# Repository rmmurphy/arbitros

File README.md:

# Introduction
_Arbitros_ (pronounced are-bee-trose) is a lightweight real time operating system developed initially—but not solely— for the Atmel XMEGA 8/16-bit series microcontroller. The name _arbitros_ is a fusion between the Latin arbitror (meaning to judge or decide) and OS (operating system). The software was developed over three years of meticulous work and is comprised of five thoroughly tested modular core components named **RTOS**, **HAL**, **UTILITIES**, **DRIVERS**, and **PACKAGES**. These components were designed to abstract common functionality, providing a user-space application with a modular, readable, layered architecture as seen in the figure below.

## Modular Core Components

### RTOS

The RTOS module performs kernel operations such as thread, semaphore, and file management;in addition to priority based task switching, driver management, time management, error handling, inter-thread communication (mailboxing), watchdog management, system debug management, and system terminal control.

### HAL

The hardware abstraction layer provides a common interface for an application when communicating with the following device specific peripherals: ADCs, clocks, DMAs, EEPROM, GPIOs, PMIC, SPIs, timers, TWIs, UARTs, and watchdog timers.

### UTILITIES

The UTILITIES module consists of software designed to help with common programming tasks such as buffer, linked-list, and state-machine management. Additionally, the module contains a mathematical library designed to perform floating and fixed-point operations such as multiply, divide, cos, sin, atan2, log10, alog10, and sqrt. In addition to these common math routines, the package contains software for performing floating point matrix operations such as inversion, transposition, addition, subtraction, multiplication, division, normalization, and eigenvalue decomposition.

### DRIVERS

A collection of Linux inspired device drivers that control a variety of external components such as Sparkfun’s 9 DOF sensor module, Newhaven’s serial character LCD module, a generic pan/tilt servo, micro SD cards, sonar modules, the RN-XV wifly module, and a terminal window controller.

### PACKAGES

External open source libraries such as libfat32, modified to operate within the _arbitros_ framework.

## Designed with Portability in Mind

Although _arbitros_ currently works with the Atmel atxmega128A1, the software was designed to be completely portable—simply modify the contents of the ‘HAL’ layer in order to port the core components to a multitude of processor architectures.

# Why was _arbitros_ Created?

## Easy to use and rich in capability

_Abitros_ was created to fit a gap in the hobbyist market. Development platforms such as Arduino were originally designed for individuals with minimal or no programming experience. As a result, their monolithic software architecture is limiting—lacking many of the features of a higher level multi-threaded operating environment. Conversely, single board computers like Raspberry Pi’s were intended for experienced programmers providing a richer set of capability; however, setting up the build environment (installing the root file system and cross compilation tools) to run Linux is a daunting task—even for seasoned professionals. 
_Arbitros_ combines the best attributes of Arduino—simplicity—with that of Linux based systems—capability—in one easy to use package. 

## Standardized Software Interfaces
Unlike Arduino, _arbitros_ incorporates Linux inspired function calls such as open, close, read, write, and ioctl in order to abstract–from the user–the intricate details that define how a driver communicates with an off-chip device (such as a shield). As seen in the example below, this framework allows a user-space application to interact with a particular entity–for instance a WIFI module–without having to know the specific details about how the device is controlled (such as the particular UART and GPIO ports used). Furthermore, this driver "blue print" makes it easier for a hobbyist to upgrade external hardware capability without effecting existing _arbitros_ user-space software applications. For example, imagine that a hobbyist has developed an _arbitros_ application that controls an autonomous vehicle using inputs from Sparkfun’s 9DOF sensor module . At a future date the hobbyist decides to upgrade the IMU to a newer more capable model. With _arbitros_ this is easy, the hobbyist simply swaps the old device driver for the new one–without requiring changes to his/her user-space application software. 

# What Runs _arbitros_?
## Sparkfun XMega100 Breakout, Atmel XMEGA-A1 Xplained, and Primus Development Board

In order to highlight the capability of _arbitros_ a development board named _Primus_ was created. As seen in the picture, _Primus_ evolved from Sparkfun’s XMega100 Breakout board (https://www.sparkfun.com/products/9546) and the architecture was designed using Sparkfun’s design rules and Eagle parts library. Although _Primus_ is a more robust solution (offering PDI debugging, USB console, and a fat32 filesystem) _arbitros_ can still operate on Sparkfun's XMega100 Breakout and Atmel's XMEGA-A1 Xplained (http://www.atmel.com/tools/XMEGA-A1XPLAINED.aspx).

# What can _arbitros_ do?
## Console with Fat32 File System

As seen in the putty window, _abitros_ offers a rich set of Linux inspired console commands. The first directive ’ls’, outputs a list of all directories and files currently stored on the SD card. In this example, only the 'LOGS' directory with the file 'DMSG.TXT' is present. These particular files are created during system initialization and used by the kernel for logging debug ‘printf’ messages. Looking closely at the terminal output, one can see that directories are traversed in a familiar way via the ‘cd’ command. In order to promote readability, the root directory is highlighted green and all subsequent directories are highlighted red. The third directive ’help’ tells the system to display a list of the sytem commands recognized by the kernel. Finally, the instruction ’dev’, displays a list of device drivers registered with the kernel and their corresponding number of open handles. In this example only the  status (LED controller), console, and SD drivers have been registered.

Looking closely at the second figure below, the command ’top’ displays metrics describing the size of various memory sections (.data, .bss, and .heap) including the amount RAM left on the system. Additionally, ’top’ shows an estimate of processor loading, which is comprised of metrics averaged over a one and five minute interval. This feature allows an _abitros_ developer to tune the performance of a particular thread or collection of threads in order to minimize the burden on the system. The instruction ’sdl’ with argument 0,1, or 2 turns on one of the kernel’s three prioritized debug levels. As seen in the example, ’sdl 0’ enables the lowest priority debug level, displaying a message every time the ‘idle’ thread resets the system watchdog timer. Increasing the debug level, such as configuring ’sdl 1’ (or 2), will tell the kernel to print all messages with the same or higher priority. The ability to display debug messages based on priority eases software integration, allowing a developer to "de-clutter" the terminal output by informing the kernel to highlight the most important information. The final command ’head’, tells the kernel to print the contents of one of the files stored on the SD card. As seen in the example, the debug log was displayed ( ‘/logs/dmsg.txt’), showing the results from the previous ‘sdl 0’ debug session.

## Attitude Heading Reference System Sensor Fusion

As part of the core ‘DRIVERS’ package, _abitros_ offers a device driver designed to fuse the measurements from Sparkfun’s 9DOF sensor module using a 9-state fixed-point error-state Kalman filter. Unlike other hobbyist sensor fusion systems available on the market , _abitros‘_ Kalman filter was designed using fixed-point rather than floating point notation. This methodology decreases processor loading enabling the algorithm to update at rates in excess of 50msec—vastly improving  the tracking capability of fast maneuvering objects. Moreover, the Kalman filter not only corrects for attitude and heading error, but it corrects gyro  bias and axis misalignment as well. In addition to the nominal filtering operations, the device driver performs magnetometer and accelerometer calibration using a ellipsoid fitting routine. Again, unlike other open source AHRS systems that perform calibration external to the microcontroller (using Matlab); _abitros‘_ AHRS performs the calibration natively using matrix operations from its built in math library (utl_math.c) provided in the ‘UTILITIES’ package. 

## Interactive AHRS GUI (arhsGui.py)

In order to demonstrate the capability of _abitros’_ sensor fusion system, an interactive graphical user interface was created using a combination of Pyqt and Pyopengl. As seen in the figure, the GUI displays three main views. The first view (‘3D’), shows a 3D orientation of the sensor along with heading (i.e. compass) and roll/pitch instrumentation. The second view (‘XY’), displays real-time plots of the roll, pitch, and yaw. Colors are used to differentiate measurement types  with green representing raw meter readings, yellow representing Kalman filtered readings, and red highlighting the difference between filtered and non-filtered measurements. The final view ‘Calibration’, controls calibration of the magnetometer and accelerometer showing the pre and post calibration data by way of the green and red point cloud.

# Getting started

The examples directory (https://github.com/rmmurphy/arbitros/raw/master/boards/primus/examples) has three folders containing software–with accompanying Atmel Studio 6 projects (http://www.atmel.com/microsite/atmel_studio6) —that demonstrate the capability of the _abitros_ operating system and _Primus_ development board. The first folder, ‘ins’, contains the AHRS software and Python GUI discussed in detail in the section titled, **What can _arbitros_ do?**. The second folder, ‘mathEval’, provides software comparing the performance differences between _abitros’_ native math library (utl_math.c) and the standard ANSII mathematics library (math.h). The final folder, ‘primusEval’, provides examples on using various _abitros_ software components such as semaphores, mailbox modules, and peripherals.

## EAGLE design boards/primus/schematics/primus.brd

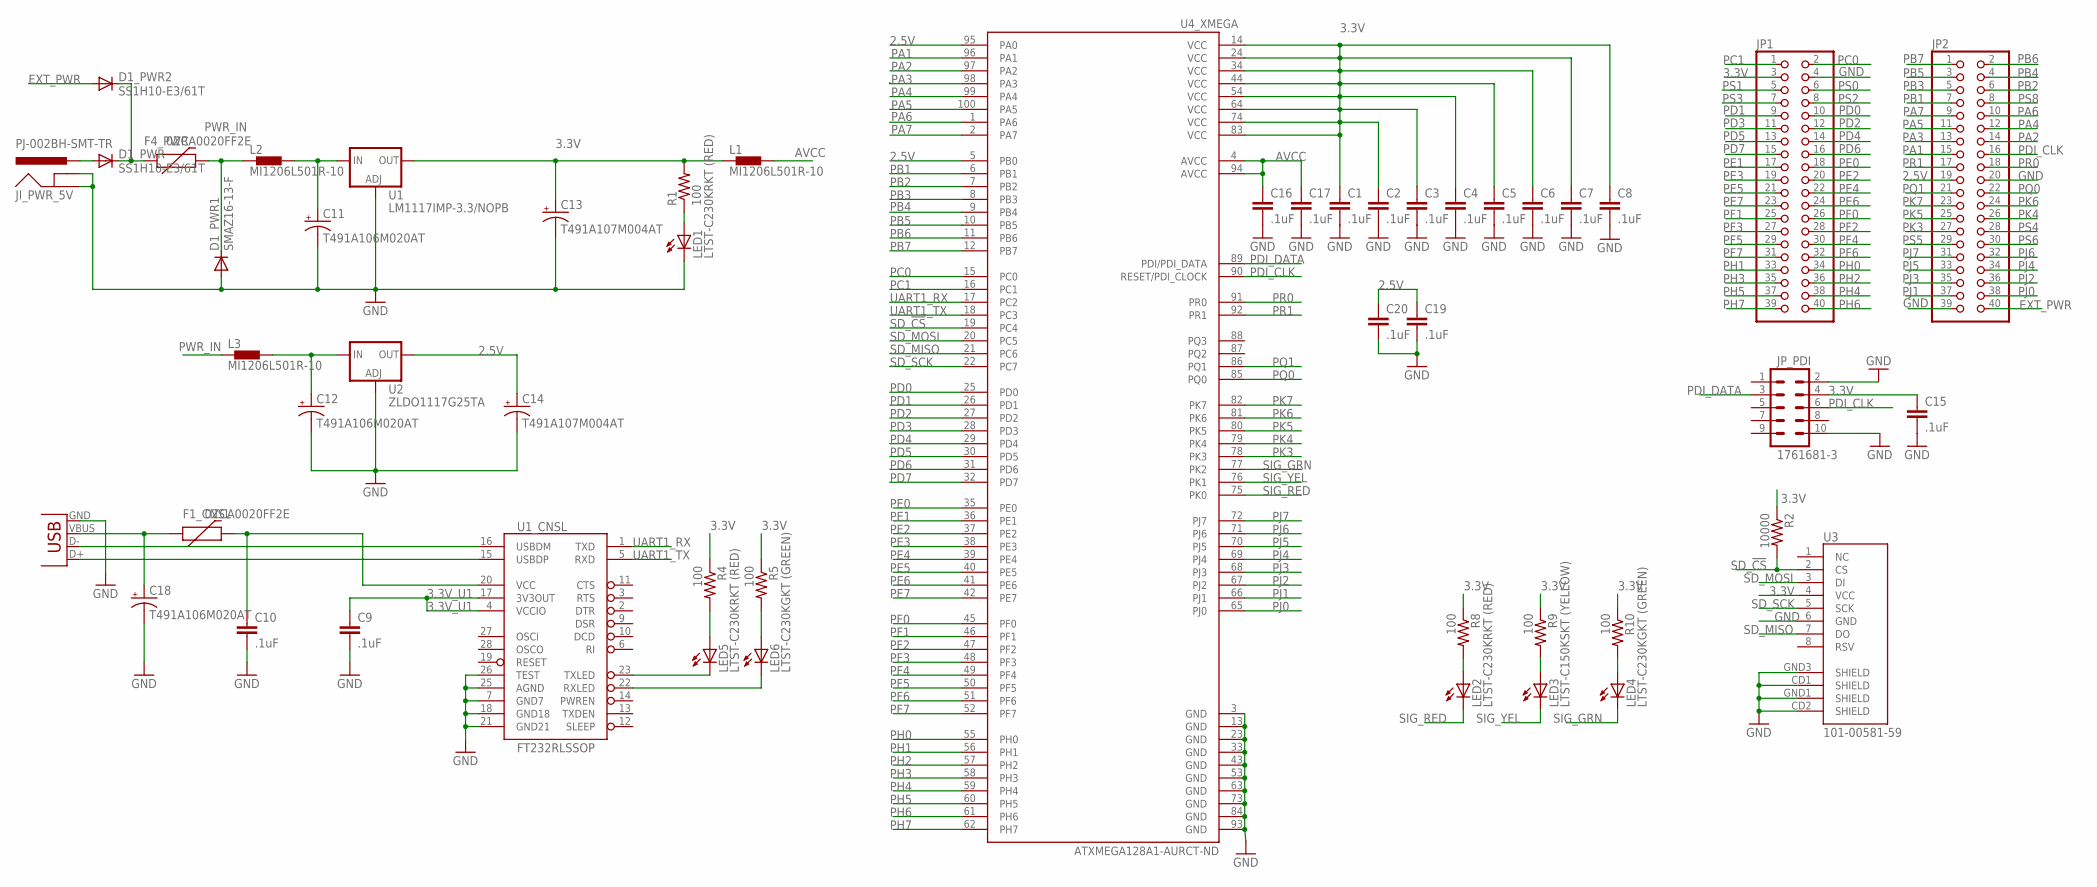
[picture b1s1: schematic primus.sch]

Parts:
C1, C2, C3, C4, C5, C6, C7, C8, C9, C10, C15, C16, C17, C19, C20: .1uF; 0603-CAP
C11, C12, C18: T491A106M020AT; EIA3216
C13, C14: T491A107M004AT; EIA3216
D1_PWR, D1_PWR2: SS1H10-E3/61T; SMA-DIODE
D1_PWR1: SMAZ16-13-F; SMA-DIODE
F1_CNSL, F4_PWR: 0ZCA0020FF2E; PTC-1206
JI_PWR_5V: PJ-002BH-SMT-TR; POWER_JACK_SMD
JP1, JP2: PINHD-2X20; 2X20
JP_PDI: 1761681-3; 2X5-SHROUDED
L1, L2, L3: MI1206L501R-10; 1206
LED1, LED2, LED5: LTST-C230KRKT (RED); LED-1206
LED3: LTST-C150KSKT (YELLOW); LED-1206
LED4, LED6: LTST-C230KGKT (GREEN); LED-1206
R1, R4, R5, R8, R9, R10: 100; 0603-RES
R2: 10000; 0603-RES
U1: LM1117IMP-3.3/NOPB; SOT223
U1_CNSL: FT232RLSSOP; SSOP28DB
U2: ZLDO1117G25TA; SOT223
U3: 101-00581-59; MICRO-SD-SOCKET-PP
U4_XMEGA: ATXMEGA128A1-AURCT-ND; TQFP-100-14X14MM
X2_CNSL: UX60A-MB-5ST; USB-MINIB

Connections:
2.5V: C14.A (+), C19.1, C20.1, JP2.19, U2.2 (OUT), U4_XMEGA.5 (PB0), U4_XMEGA.95 (PA0)
3.3V: C1.1, C2.1, C3.1, C4.1, C5.1, C6.1, C7.1, C8.1, C13.A (+), C15.1, JP1.3, JP_PDI.4, L1.1, R1.2, R2.1, R4.1, R5.1, R8.1, R9.1, R10.1, U1.2 (OUT), U3.4 (VCC), U4_XMEGA.14 (VCC), U4_XMEGA.24 (VCC), U4_XMEGA.34 (VCC), U4_XMEGA.44 (VCC), U4_XMEGA.54 (VCC), U4_XMEGA.64 (VCC), U4_XMEGA.74 (VCC), U4_XMEGA.83 (VCC)
3.3V_U1: C9.1, U1_CNSL.4 (VCCIO), U1_CNSL.17 (3V3OUT)
AVCC: C16.1, C17.1, L1.2, U4_XMEGA.4 (AVCC), U4_XMEGA.94 (AVCC)
EXT_PWR: D1_PWR2.A, JP2.40
GND: C1.2, C2.2, C3.2, C4.2, C5.2, C6.2, C7.2, C8.2, C9.2, C10.2, C11.C (-), C12.C (-), C13.C (-), C14.C (-), C15.2, C16.2, C17.2, C18.C (-), C19.2, C20.2, D1_PWR1.A, JI_PWR_5V.GND (GNDBREAK), JI_PWR_5V.P$4 (GND), JP1.4, JP2.20, JP2.39, JP_PDI.2, JP_PDI.10, LED1.C, U1.1 (ADJ), U1_CNSL.7 (GND7), U1_CNSL.18 (GND18), U1_CNSL.21 (GND21), U1_CNSL.25 (AGND), U1_CNSL.26 (TEST), U2.1 (ADJ), U3.6 (GND), U3.CD1 (SHIELD), U3.CD2 (SHIELD), U3.GND1 (SHIELD), U3.GND3 (SHIELD), U4_XMEGA.3 (GND), U4_XMEGA.13 (GND), U4_XMEGA.23 (GND), U4_XMEGA.33 (GND), U4_XMEGA.43 (GND), U4_XMEGA.53 (GND), U4_XMEGA.63 (GND), U4_XMEGA.73 (GND), U4_XMEGA.84 (GND), U4_XMEGA.93 (GND), X2_CNSL.GND
unnamed: LED5.A, R4.2
unnamed: LED6.A, R5.2
unnamed: LED2.A, R8.2
unnamed: LED3.A, R9.2
unnamed: LED4.A, R10.2
unnamed: C11.A (+), L2.2, U1.3 (IN)
unnamed: C12.A (+), L3.2, U2.3 (IN)
unnamed: D1_PWR.A, JI_PWR_5V.VIN0 (PWR)
unnamed: D1_PWR.C, D1_PWR2.C, F4_PWR.1
unnamed: LED1.A, R1.1
unnamed: C10.1, F1_CNSL.2, U1_CNSL.20 (VCC)
PA1: JP2.15, U4_XMEGA.96 (PA1)
PA2: JP2.14, U4_XMEGA.97 (PA2)
PA3: JP2.13, U4_XMEGA.98 (PA3)
PA4: JP2.12, U4_XMEGA.99 (PA4)
PA5: JP2.11, U4_XMEGA.100 (PA5)
PA6: JP2.10, U4_XMEGA.1 (PA6)
PA7: JP2.9, U4_XMEGA.2 (PA7)
PB1: JP2.7, U4_XMEGA.6 (PB1)
PB2: JP2.6, U4_XMEGA.7 (PB2)
PB3: JP2.5, U4_XMEGA.8 (PB3)
PB4: JP2.4, U4_XMEGA.9 (PB4)
PB5: JP2.3, U4_XMEGA.10 (PB5)
PB6: JP2.2, U4_XMEGA.11 (PB6)
PB7: JP2.1, U4_XMEGA.12 (PB7)
PC0: JP1.2, U4_XMEGA.15 (PC0)
PC1: JP1.1, U4_XMEGA.16 (PC1)
PD0: JP1.10, U4_XMEGA.25 (PD0)
PD1: JP1.9, U4_XMEGA.26 (PD1)
PD2: JP1.12, U4_XMEGA.27 (PD2)
PD3: JP1.11, U4_XMEGA.28 (PD3)
PD4: JP1.14, U4_XMEGA.29 (PD4)
PD5: JP1.13, U4_XMEGA.30 (PD5)
PD6: JP1.16, U4_XMEGA.31 (PD6)
PD7: JP1.15, U4_XMEGA.32 (PD7)
PDI_CLK: JP2.16, JP_PDI.6, U4_XMEGA.90 (RESET/PDI_CLOCK)
PDI_DATA: JP_PDI.3, U4_XMEGA.89 (PDI/PDI_DATA)
PE0: JP1.18, U4_XMEGA.35 (PE0)
PE1: JP1.17, U4_XMEGA.36 (PE1)
PE2: JP1.20, U4_XMEGA.37 (PE2)
PE3: JP1.19, U4_XMEGA.38 (PE3)
PE4: JP1.22, U4_XMEGA.39 (PE4)
PE5: JP1.21, U4_XMEGA.40 (PE5)
PE6: JP1.24, U4_XMEGA.41 (PE6)
PE7: JP1.23, U4_XMEGA.42 (PE7)
PF0: JP1.26, U4_XMEGA.45 (PF0)
PF1: JP1.25, U4_XMEGA.46 (PF1)
PF2: JP1.28, U4_XMEGA.47 (PF2)
PF3: JP1.27, U4_XMEGA.48 (PF3)
PF4: JP1.30, U4_XMEGA.49 (PF4)
PF5: JP1.29, U4_XMEGA.50 (PF5)
PF6: JP1.32, U4_XMEGA.51 (PF6)
PF7: JP1.31, U4_XMEGA.52 (PF7)
PH0: JP1.34, U4_XMEGA.55 (PH0)
PH1: JP1.33, U4_XMEGA.56 (PH1)
PH2: JP1.36, U4_XMEGA.57 (PH2)
PH3: JP1.35, U4_XMEGA.58 (PH3)
PH4: JP1.38, U4_XMEGA.59 (PH4)
PH5: JP1.37, U4_XMEGA.60 (PH5)
PH6: JP1.40, U4_XMEGA.61 (PH6)
PH7: JP1.39, U4_XMEGA.62 (PH7)
PJ0: JP2.38, U4_XMEGA.65 (PJ0)
PJ1: JP2.37, U4_XMEGA.66 (PJ1)
PJ2: JP2.36, U4_XMEGA.67 (PJ2)
PJ3: JP2.35, U4_XMEGA.68 (PJ3)
PJ4: JP2.34, U4_XMEGA.69 (PJ4)
PJ5: JP2.33, U4_XMEGA.70 (PJ5)
PJ6: JP2.32, U4_XMEGA.71 (PJ6)
PJ7: JP2.31, U4_XMEGA.72 (PJ7)
PK3: JP2.27, U4_XMEGA.78 (PK3)
PK4: JP2.26, U4_XMEGA.79 (PK4)
PK5: JP2.25, U4_XMEGA.80 (PK5)
PK6: JP2.24, U4_XMEGA.81 (PK6)
PK7: JP2.23, U4_XMEGA.82 (PK7)
PQ0: JP2.22, U4_XMEGA.85 (PQ0)
PQ1: JP2.21, U4_XMEGA.86 (PQ1)
PR0: JP2.18, U4_XMEGA.91 (PR0)
PR1: JP2.17, U4_XMEGA.92 (PR1)
PS0: JP1.6
PS1: JP1.5
PS2: JP1.8
PS3: JP1.7
PS4: JP2.28
PS5: JP2.29
PS6: JP2.30
PS8: JP2.8
PWR_IN: D1_PWR1.C, F4_PWR.2, L2.1, L3.1
RXLED_U1: LED6.C, U1_CNSL.22 (RXLED)
SD_!CS: R2.2, U3.2 (CS), U4_XMEGA.19 (PC4)
SD_MISO: U3.7 (DO), U4_XMEGA.21 (PC6)
SD_MOSI: U3.3 (DI), U4_XMEGA.20 (PC5)
SD_SCK: U3.5 (SCK), U4_XMEGA.22 (PC7)
SIG_GRN: LED4.C, U4_XMEGA.77 (PK2)
SIG_RED: LED2.C, U4_XMEGA.75 (PK0)
SIG_YEL: LED3.C, U4_XMEGA.76 (PK1)
TXLED_U1: LED5.C, U1_CNSL.23 (TXLED)
UART1_RX: U1_CNSL.1 (TXD), U4_XMEGA.17 (PC2)
UART1_TX: U1_CNSL.5 (RXD), U4_XMEGA.18 (PC3)
USB_D+: U1_CNSL.15 (USBDP), X2_CNSL.D+
USB_D-: U1_CNSL.16 (USBDM), X2_CNSL.D-
VBUS: C18.A (+), F1_CNSL.1, X2_CNSL.VBUS

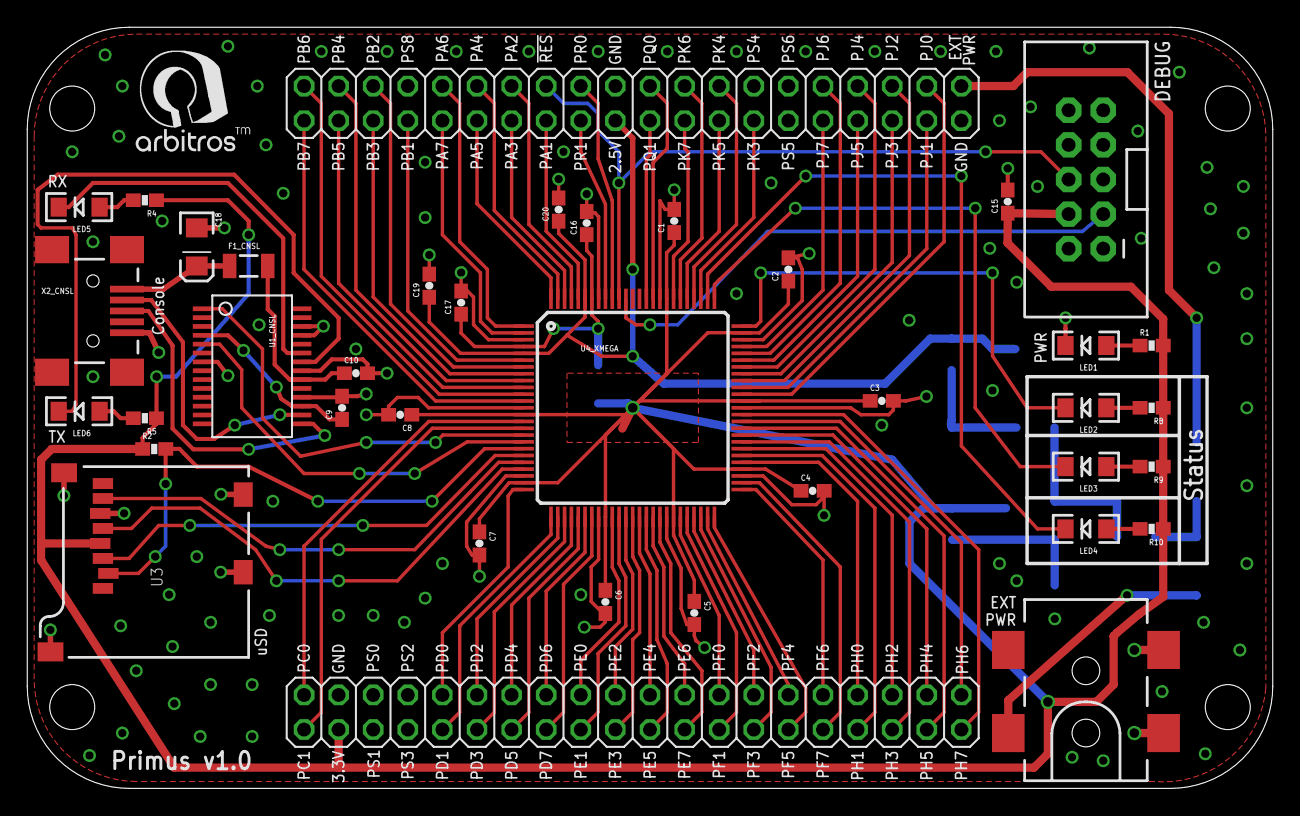
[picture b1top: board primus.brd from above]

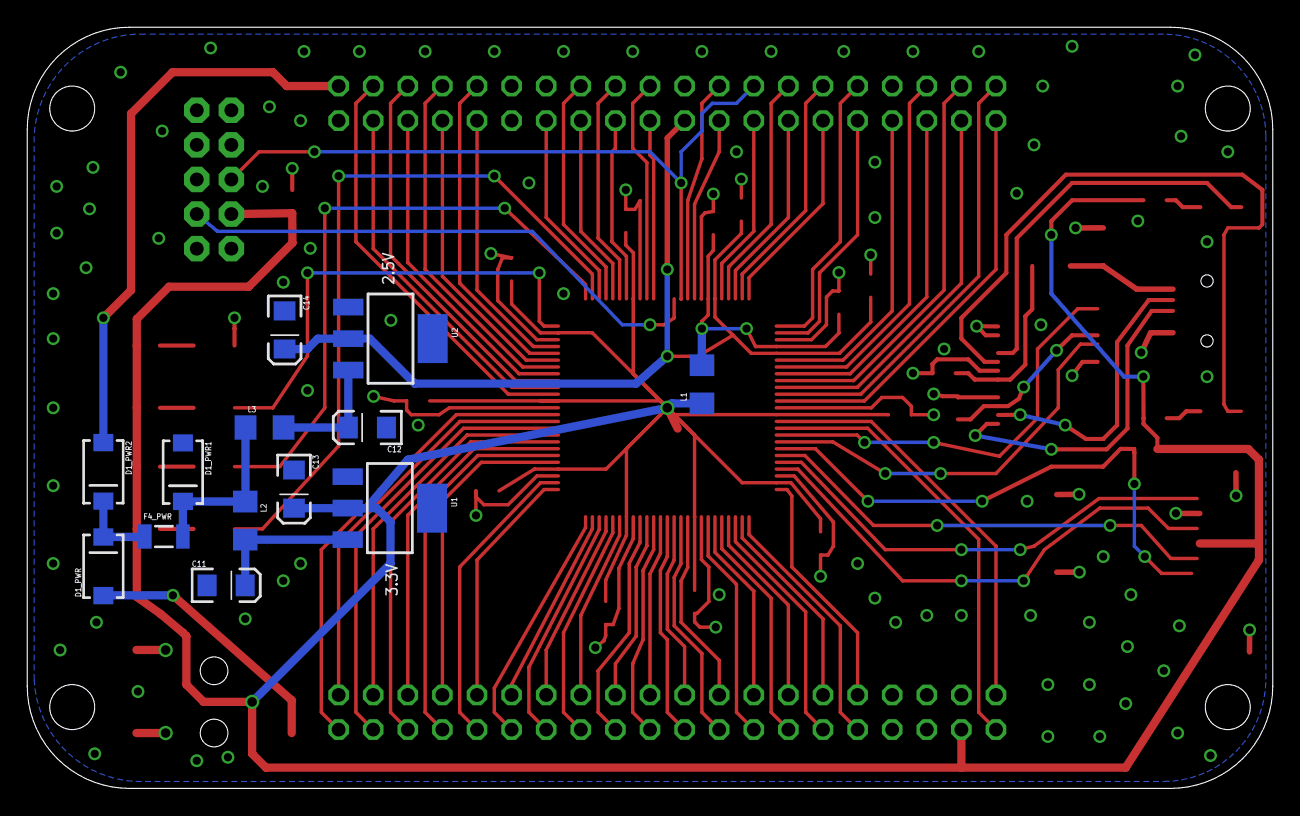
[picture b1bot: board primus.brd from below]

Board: 2 copper layers, 91.4 x 55.9 mm, 56 parts (13 on the bottom side), 99 nets.

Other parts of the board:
U$1: ARBLOGO
U$2, U$3, U$4, U$5: STAND-OFF

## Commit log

2014-05-21 Add boards
2014-05-21 Create gh-pages branch via GitHub
2014-05-22 Added IXTH96P085T
2014-05-22 Tell github to ignore certain files on checkin
2014-05-22 Added more things to ignore
2014-05-23 Allowing a commit of libs
2014-05-23 Removed doxygen directory
2014-05-23 deleted some files
2014-05-23 removed object files
2014-05-23 deleted object files
2014-05-26 Changed projects to use native avr studio 6 build tools.

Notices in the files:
parts and their libraries:
SparkFun-DigitalIC: Licensing: CC v3.0 Share-Alike You are welcome to use this library for commercial purposes.
